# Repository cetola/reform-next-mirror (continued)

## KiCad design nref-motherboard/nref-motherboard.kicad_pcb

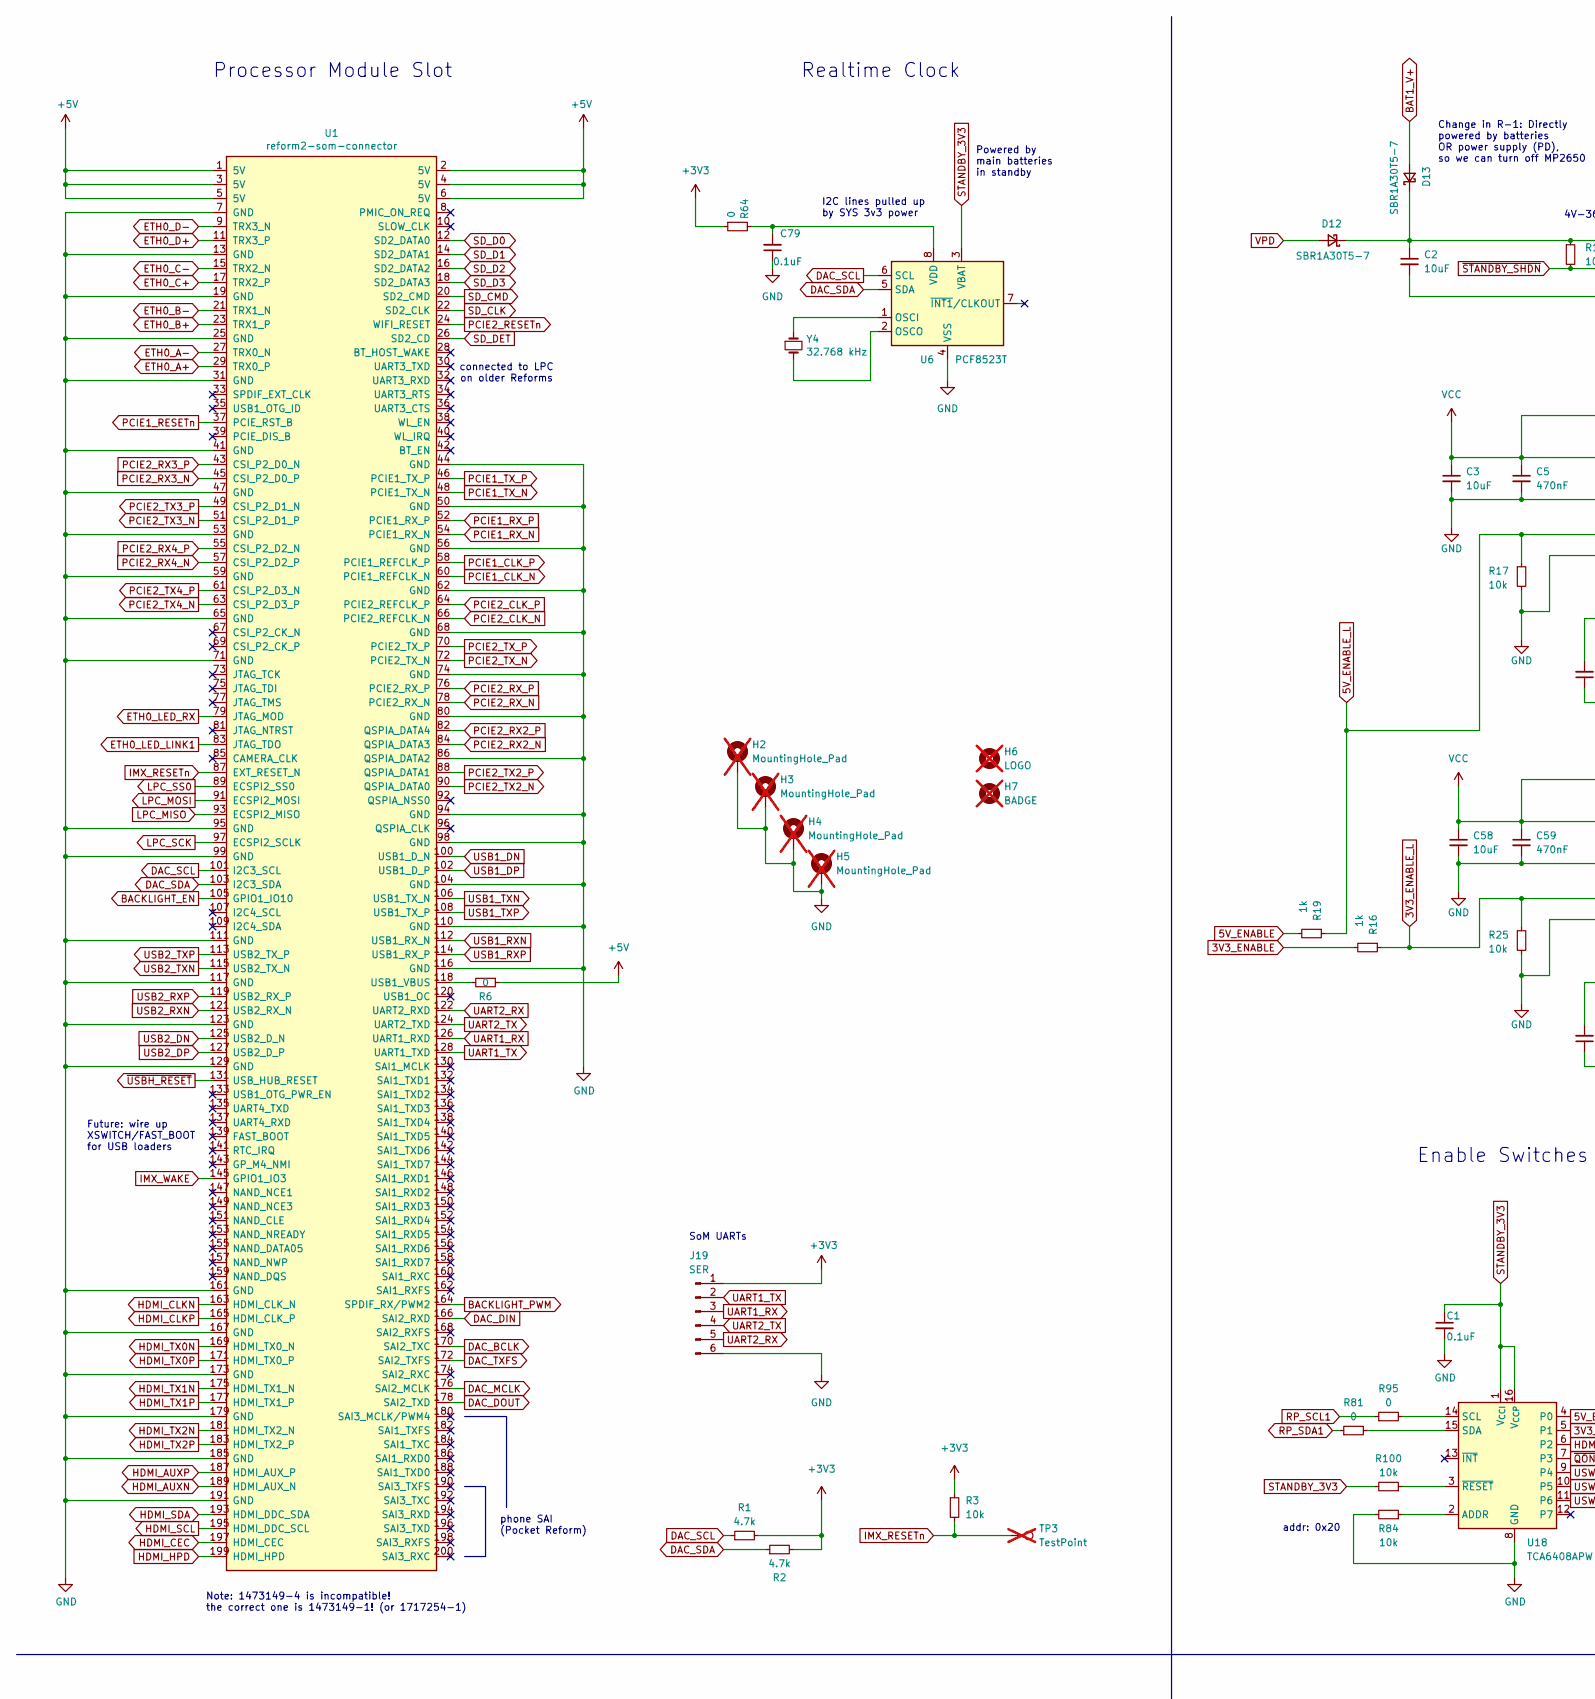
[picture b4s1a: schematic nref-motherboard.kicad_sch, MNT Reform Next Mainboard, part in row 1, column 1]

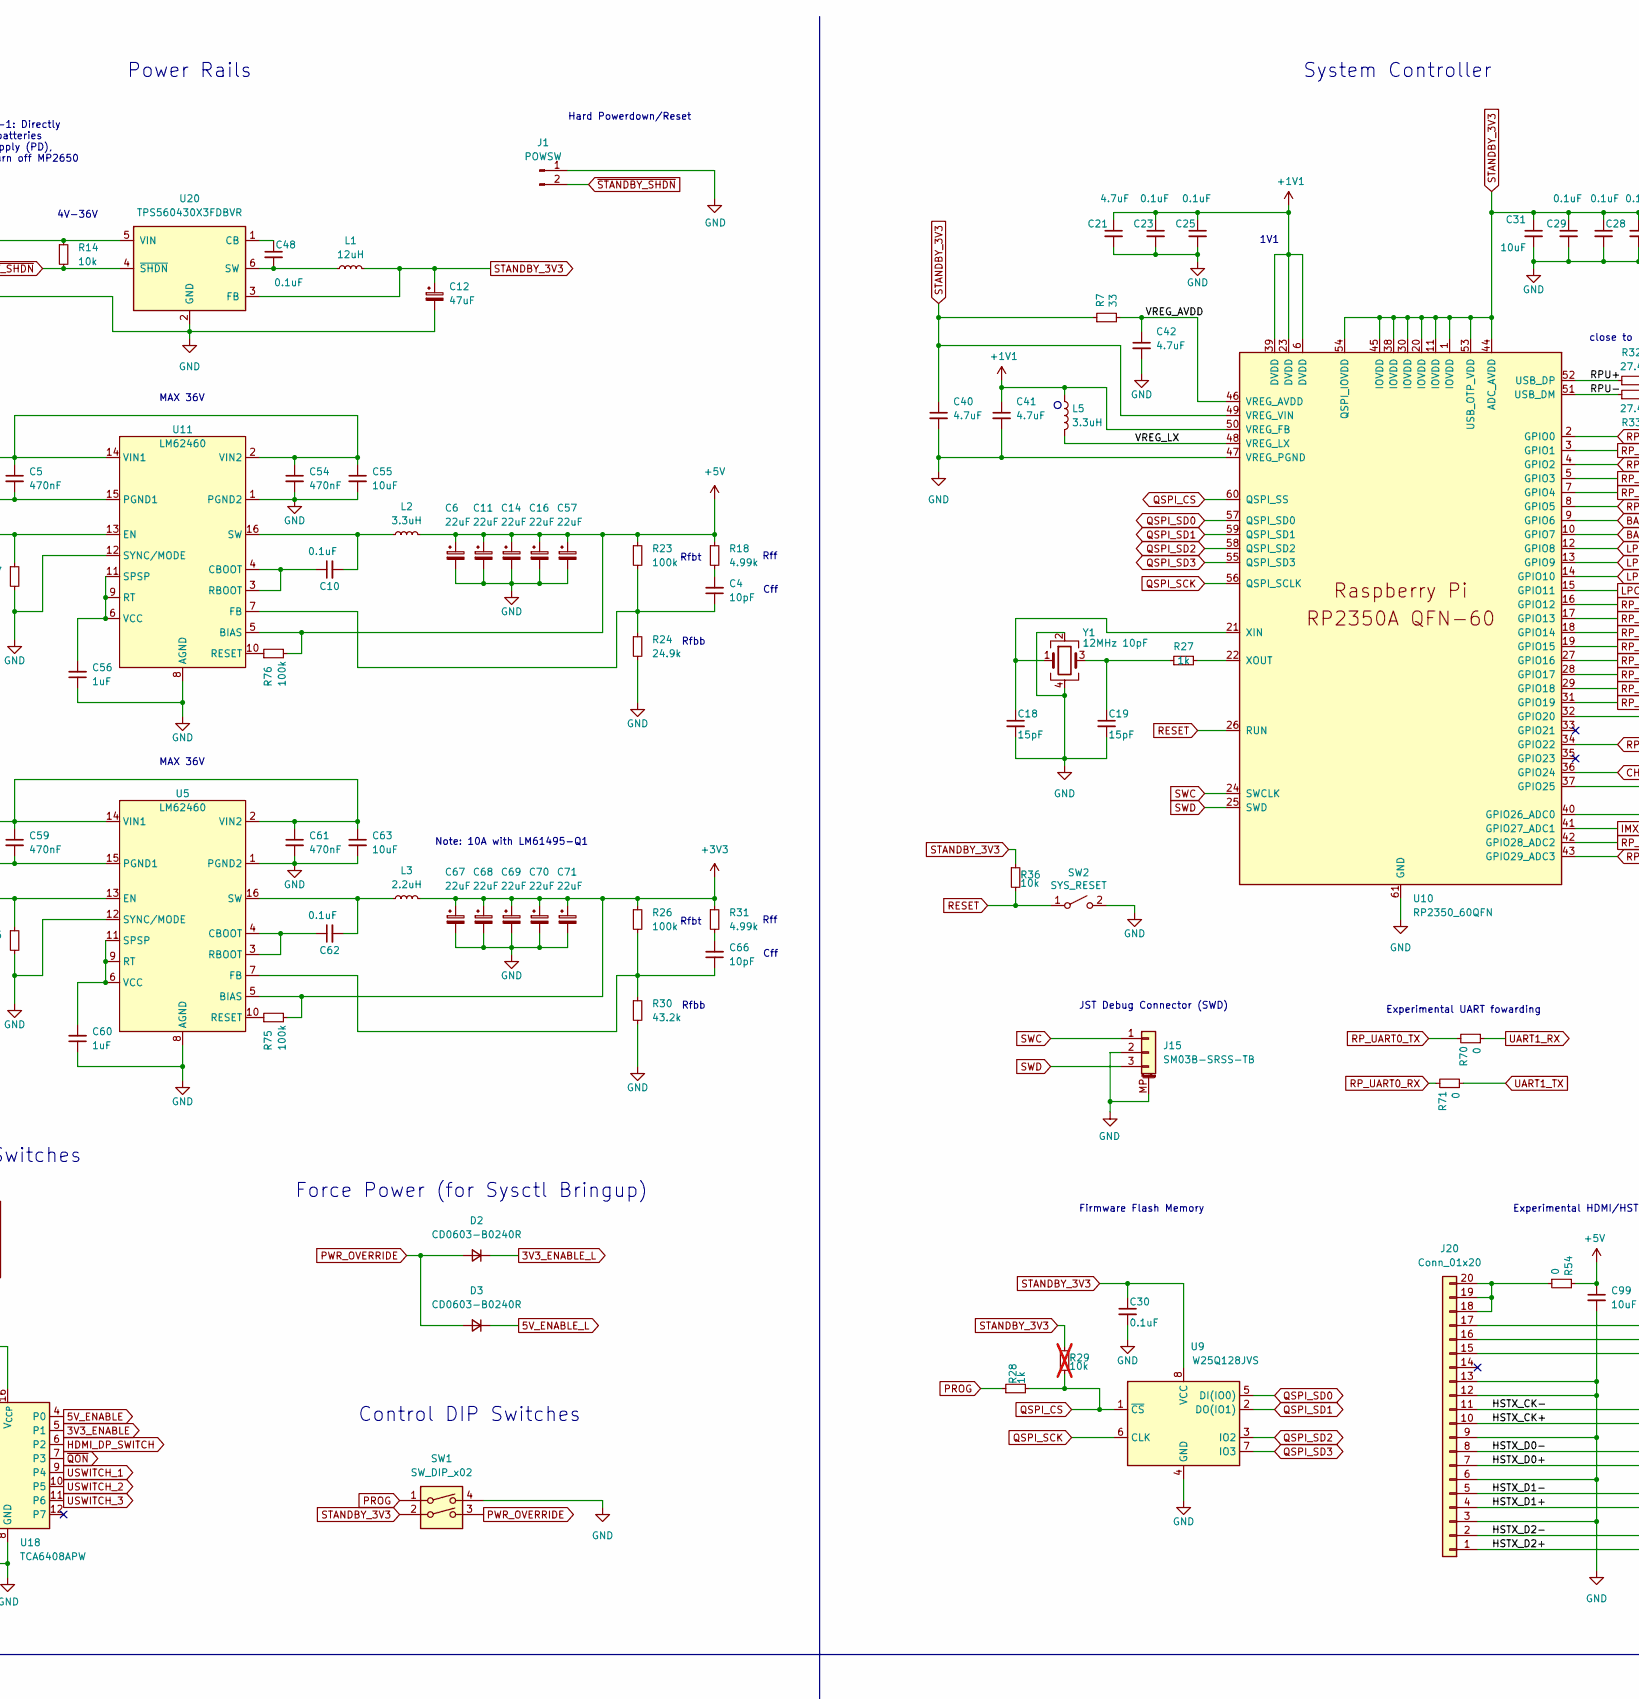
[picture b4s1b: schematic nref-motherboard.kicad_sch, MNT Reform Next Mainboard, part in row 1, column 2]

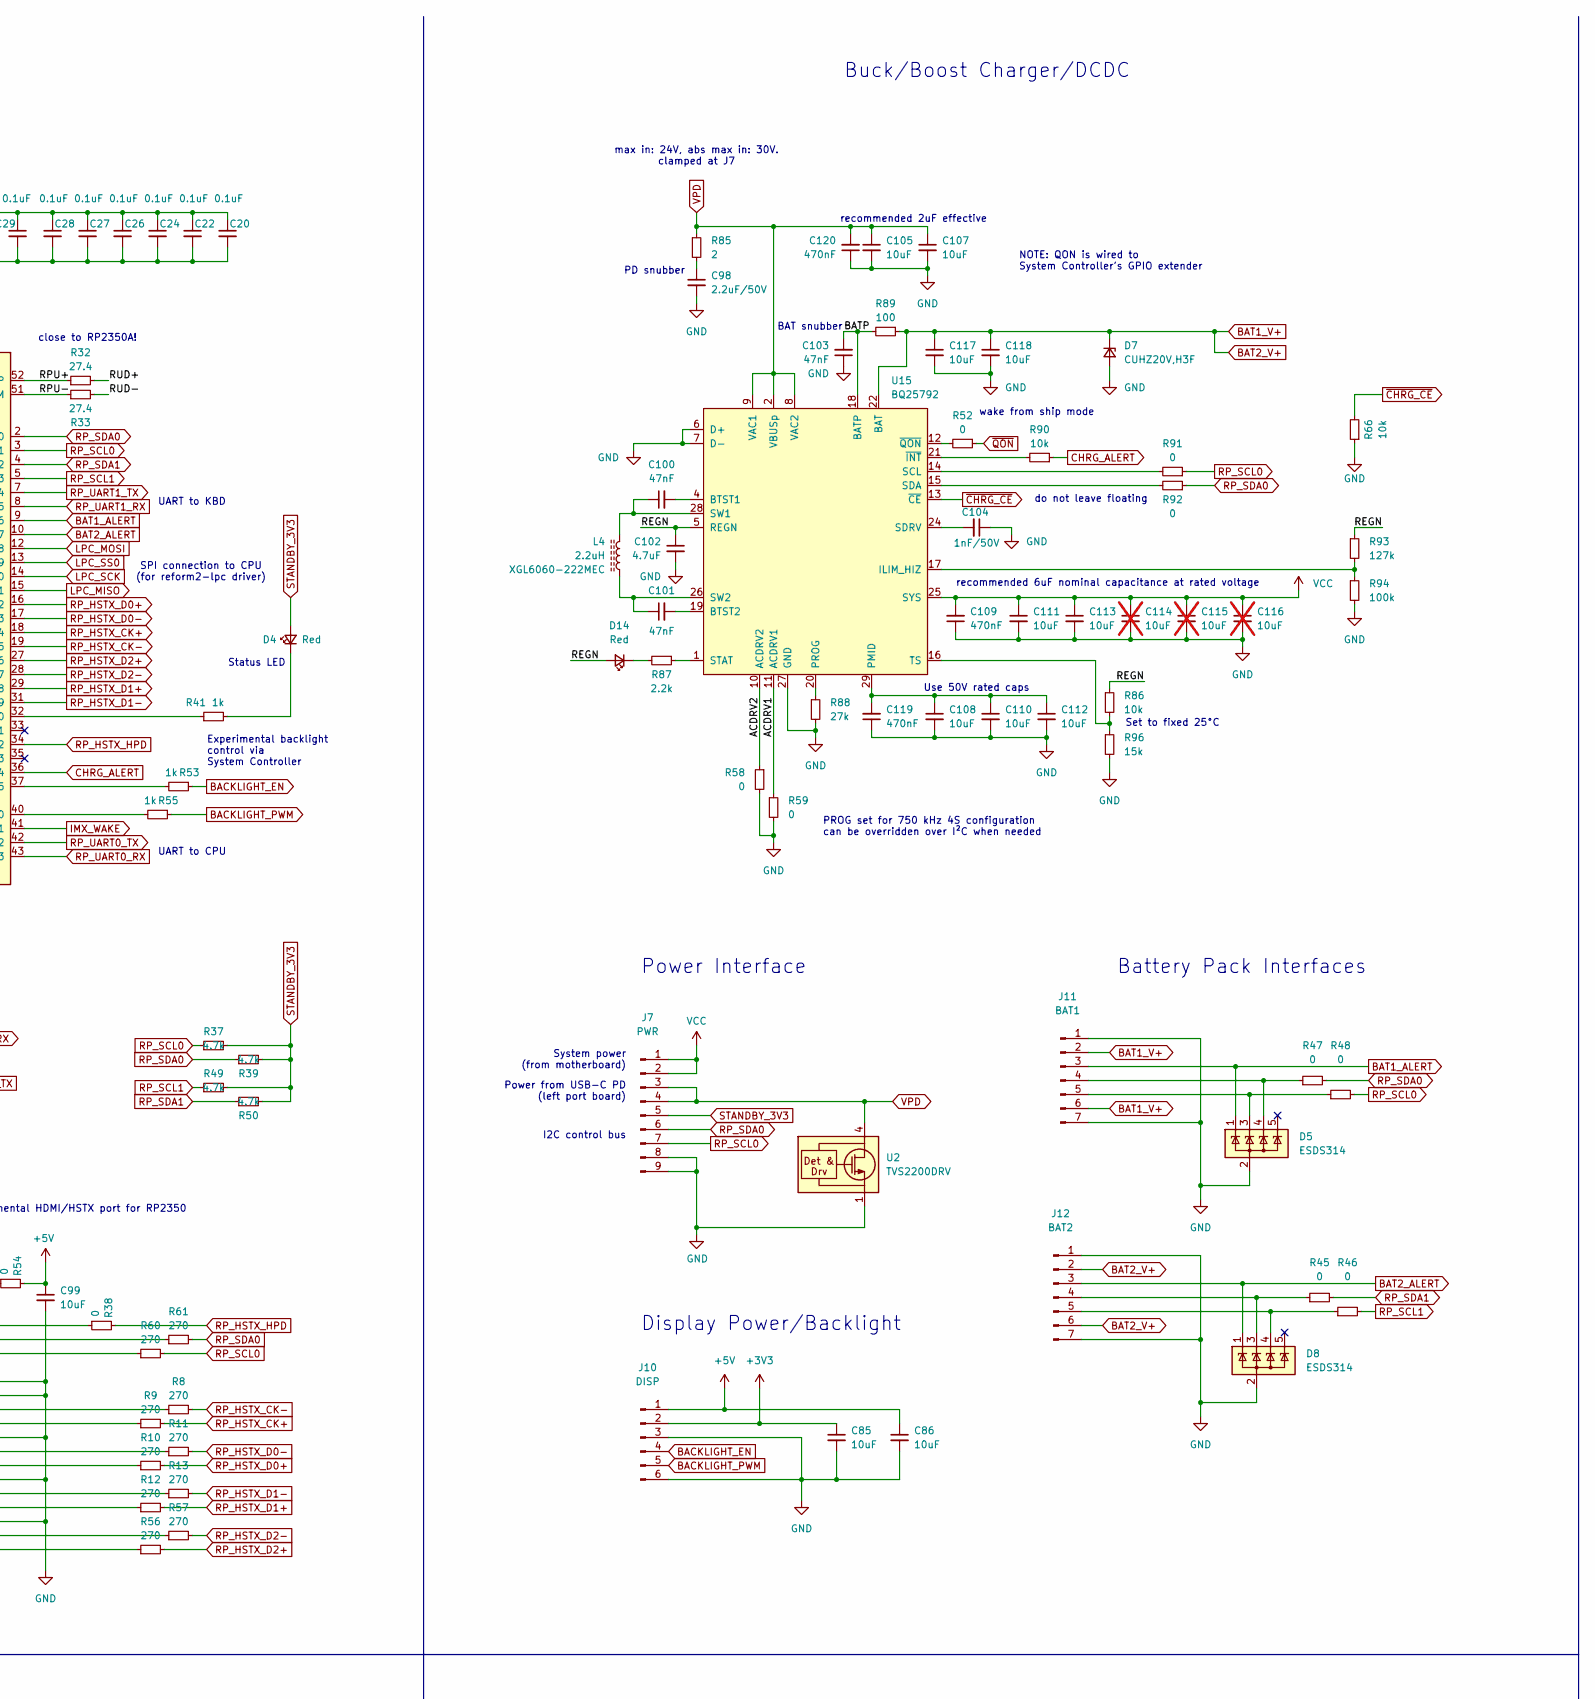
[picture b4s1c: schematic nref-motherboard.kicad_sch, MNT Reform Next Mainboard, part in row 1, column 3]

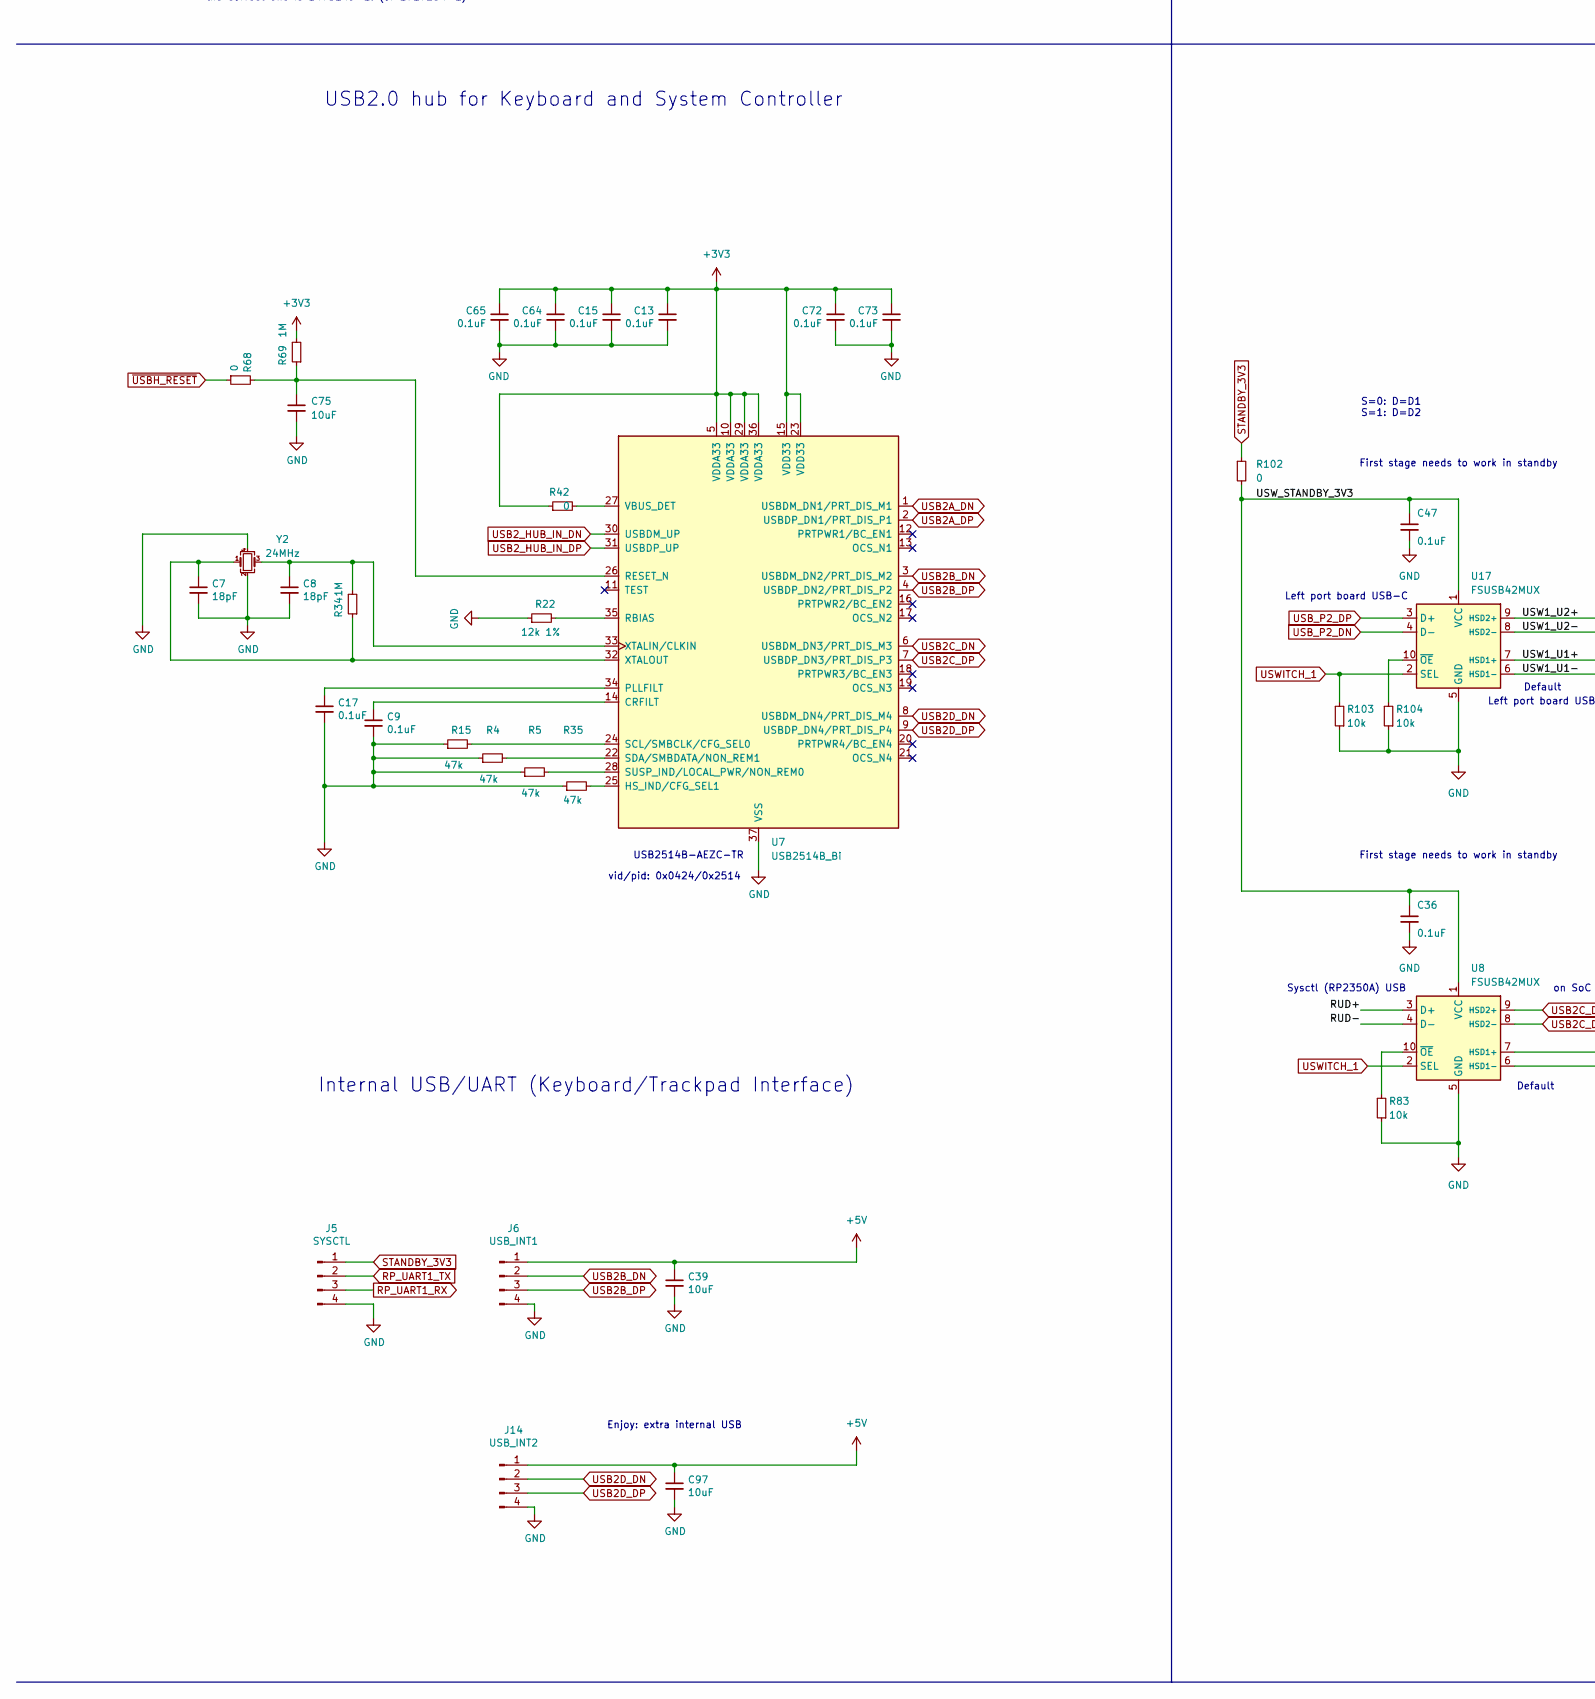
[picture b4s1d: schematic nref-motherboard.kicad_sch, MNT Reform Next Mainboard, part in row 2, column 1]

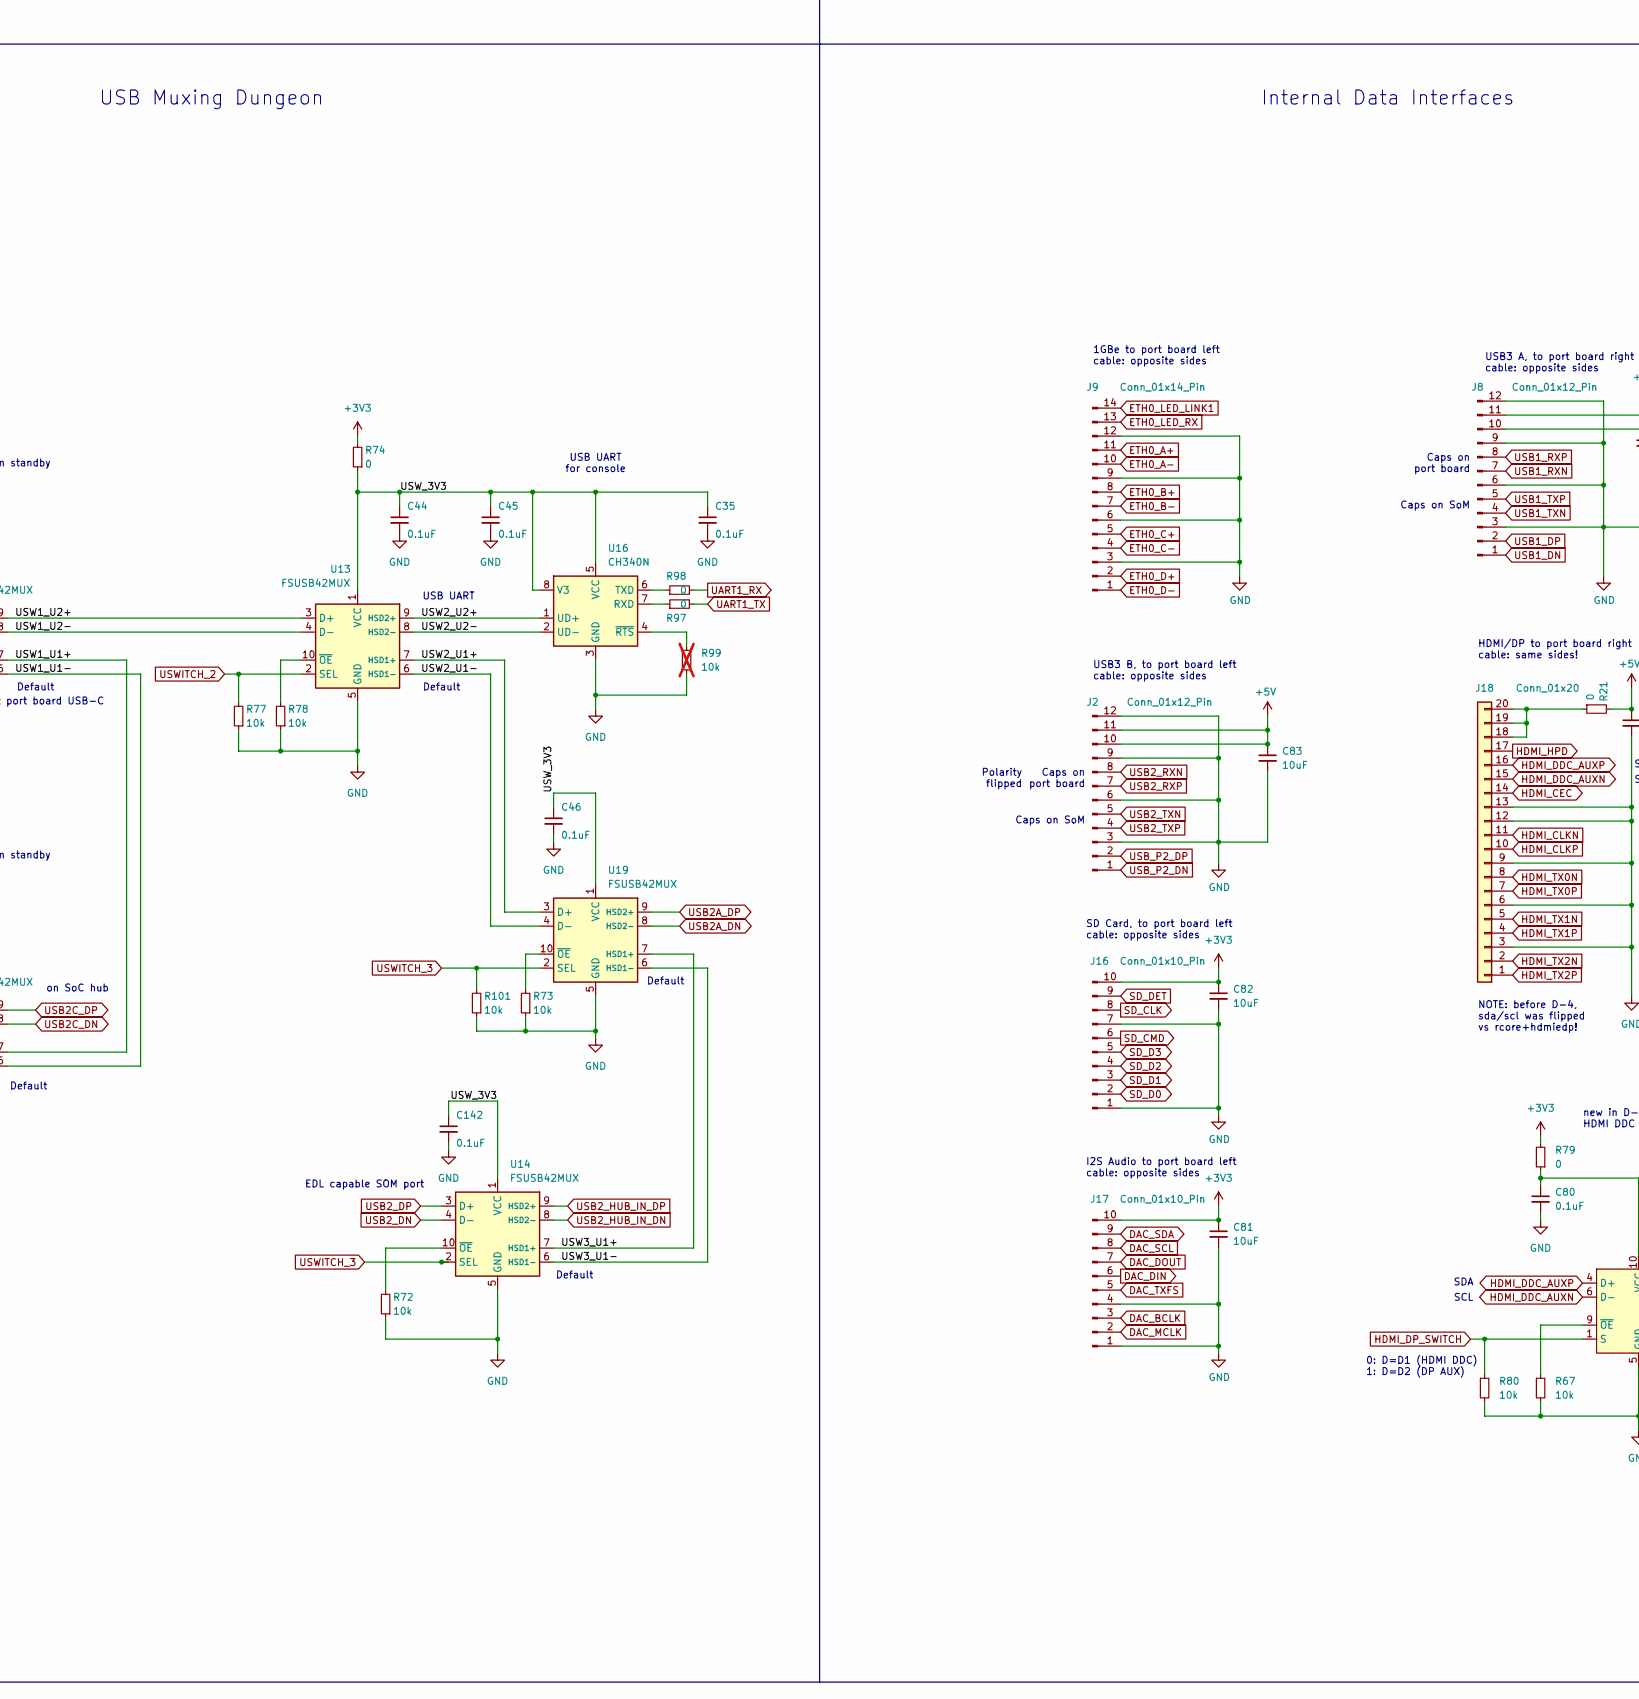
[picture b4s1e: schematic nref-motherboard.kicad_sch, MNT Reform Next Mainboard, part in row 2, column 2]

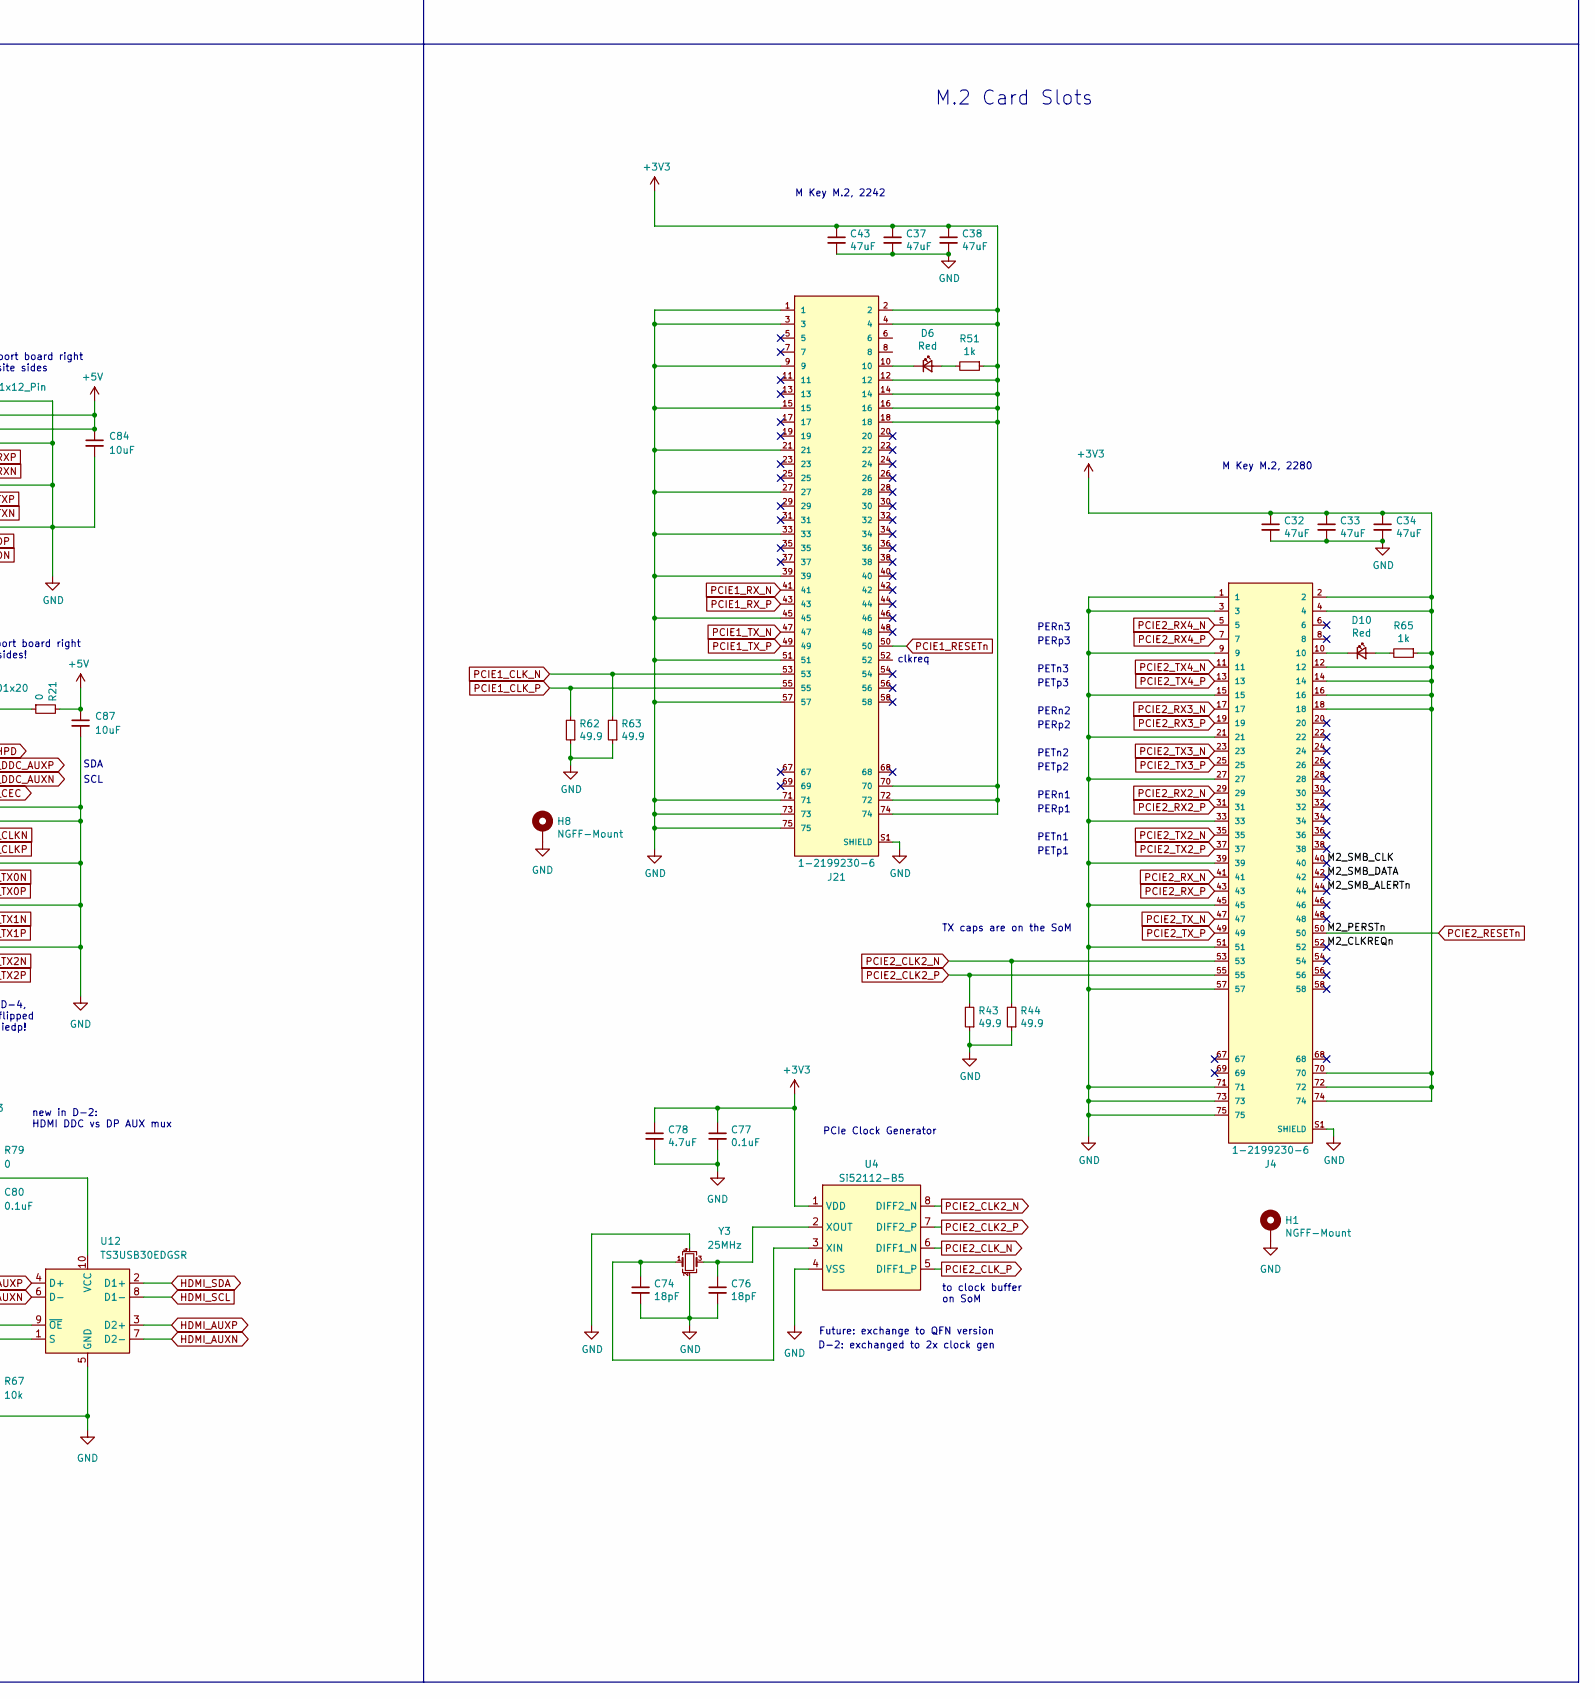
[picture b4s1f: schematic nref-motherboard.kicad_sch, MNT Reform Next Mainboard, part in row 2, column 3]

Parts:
C1, C9, C10, C13, C15, C17, C20, C22, C23, C24, C25, C26, C27, C28, C29, C30, C35, C36, C44, C45, C46, C47, C48, C62, C64, C65, C72, C73, C77, C79, C80, C142: 0.1uF; C_0402_1005Metric; LCSC C1525
C2, C3, C31, C39, C55, C58, C63, C75, C81, C82, C83, C84, C85, C86, C87, C97, C99: 10uF; C_0603_1608Metric; LCSC C92487
C4, C66: 10pF; C_0402_1005Metric; LCSC C32949
C5, C54, C59, C61: 470nF; C_0603_1608Metric; LCSC C170149
C6, C11, C14, C16, C57, C67, C68, C69, C70, C71: 22uF; C_0603_1608Metric; LCSC C361061
C7, C8, C74, C76: 18pF; C_0402_1005Metric; LCSC C1549
C12, C32, C33, C34, C37, C38, C43: 47uF; C_0603_1608Metric; LCSC C140782
C18, C19: 15pF; C_0603_1608Metric; LCSC C1644
C21, C41: 4.7uF; C_0603_1608Metric; LCSC C19666
C40, C42, C78, C102: 4.7uF; C_0402_1005Metric; LCSC C23733
C56, C60: 1uF; C_0402_1005Metric; LCSC C52923
C98: 2.2uF/50V; C_1206_3216Metric; LCSC C50254
C100, C101, C103: 47nF; C_0402_1005Metric; LCSC C272875
C104: 1nF/50V; C_0402_1005Metric; LCSC C1523
C105, C107, C108, C110, C112, C117, C118: 10uF; C_0805_2012Metric; LCSC C440198
C109, C119, C120: 470nF; C_0402_1005Metric; LCSC C437527
C111, C113: 10uF; C_1206_3216Metric; LCSC C13585
C114, C115, C116: 10uF; C_0603_1608Metric; not fitted
D2, D3: CD0603-B0240R; D_0603_1608Metric; LCSC C3312582
D4, D6, D10, D14: Red; LED_0603_1608Metric; LCSC C83242
D5, D8: ESDS314; SOT-23-5; LCSC C1847859
D7: CUHZ20V,H3F; D_SOD-323; LCSC C2857019
D12, D13: SBR1A30T5-7; D_SOD-323; LCSC C53100376
H1, H8: NGFF-Mount; WA-SMSI-M2; LCSC C22431324
H2, H3, H4, H5: MountingHole_Pad; MountingHole_2.5mm_Pad; not fitted
H6: LOGO; nref-logo; not fitted
H7: BADGE; nref-motherboard-badge; not fitted
J1: POWSW; JST_SH_SM02B-SRSS-TB_1x02-1MP_P1.00mm_Horizontal; LCSC C160402
J2, J8: Conn_01x12_Pin; Hirose_FH12-12S-0.5SH_1x12-1MP_P0.50mm_Horizontal; LCSC C2906115
J4, J21: 1-2199230-6; TE_1-2199230-6; LCSC C4710843
J5: SYSCTL; JST_SH_SM04B-SRSS-TB_1x04-1MP_P1.00mm_Horizontal; LCSC C160404
J6: USB_INT1; JST_SH_SM04B-SRSS-TB_1x04-1MP_P1.00mm_Horizontal; LCSC C160404
J7: PWR; JST_SH_SM09B-SRSS-TB_1x09-1MP_P1.00mm_Horizontal; LCSC C160408
J9: Conn_01x14_Pin; Hirose_FH12-14S-0.5SH_1x14-1MP_P0.50mm_Horizontal; LCSC C2906116
J10: DISP; JST_SH_SM06B-SRSS-TB_1x06-1MP_P1.00mm_Horizontal; LCSC C160405
J11: BAT1; JST_SH_SM07B-SRSS-TB_1x07-1MP_P1.00mm_Horizontal; LCSC C160406
J12: BAT2; JST_SH_SM07B-SRSS-TB_1x07-1MP_P1.00mm_Horizontal; LCSC C160406
J14: USB_INT2; JST_SH_SM04B-SRSS-TB_1x04-1MP_P1.00mm_Horizontal; LCSC C160404
J15: SM03B-SRSS-TB; JST_SH_SM03B-SRSS-TB_1x03-1MP_P1.00mm_Horizontal; LCSC C160403
J16, J17: Conn_01x10_Pin; Hirose_FH12-10S-0.5SH_1x10-1MP_P0.50mm_Horizontal; LCSC C2906114
J18, J20: Conn_01x20; Hirose_FH12-20S-0.5SH_1x20-1MP_P0.50mm_Horizontal; LCSC C2906119
J19: SER; JST_SH_SM06B-SRSS-TB_1x06-1MP_P1.00mm_Horizontal; LCSC C160405
L1: 12uH; L_Taiyo-Yuden_NR-30xx; LCSC C167758
L2: 3.3uH; L_Coilcraft_XAL6060-XXX; LCSC C3040366
L3: 2.2uH; L_Coilcraft_XAL6060-XXX; LCSC C167218
L4: 2.2uH; L_Coilcraft_XAL6060-XXX; MPN XGL6060-222MEC; LCSC C3911671
L5: 3.3uH; L_pol_2016; LCSC C42411119
R1, R2, R37, R39, R49, R50: 4.7k; R_0402_1005Metric; LCSC C25900
R3, R14, R17, R25, R36, R66, R67, R72, R73, R77, R78, R80, R83, R84, R86, R90, R100, R101, R103, R104: 10k; R_0402_1005Metric; LCSC C25744
R4, R5, R15, R35: 47k; R_0402_1005Metric; LCSC C25792
R6, R21, R38, R42, R45, R46, R47, R48, R52, R54, R58, R59, R64, R68, R70, R71, R74, R79, R81, R91, R92, R95, R97, R98, R102: 0; R_0402_1005Metric; LCSC C17168
R7: 33; R_0402_1005Metric; LCSC C25105
R8, R9, R10, R11, R12, R13, R56, R57, R60, R61: 270; R_0402_1005Metric; LCSC C25099
R16, R19, R27, R28, R41, R51, R53, R55, R65: 1k; R_0402_1005Metric; LCSC C11702
R18, R31: 4.99k; R_0402_1005Metric; LCSC C25903
R22: 12k 1%; R_0402_1005Metric; LCSC C25752
R23, R26, R75, R76: 100k; R_0402_1005Metric; LCSC C25741
R24: 24.9k; R_0402_1005Metric; LCSC C25874
R29: 10k; R_0402_1005Metric; LCSC C60490; not fitted
R30: 43.2k; R_0402_1005Metric; LCSC C25894
R32, R33: 27.4; R_0402_1005Metric; LCSC C31439
R34, R69: 1M; R_0402_1005Metric; LCSC C26083
R43, R44, R62, R63: 49.9; R_0402_1005Metric; LCSC C25120
R85: 2; R_0603_1608Metric; LCSC C22977
R87: 2.2k; R_0402_1005Metric; LCSC C25879
R88: 27k; R_0402_1005Metric; LCSC C25771
R89: 100; R_0402_1005Metric; LCSC C25076
R93: 127k; C_0603_1608Metric; LCSC C22869
R94: 100k; C_0603_1608Metric; LCSC C25803
R96: 15k; R_0402_1005Metric; LCSC C25756
R99: 10k; R_0402_1005Metric; LCSC C25744; not fitted
SW1: SW_DIP_x02; SW_DIP_SPSTx02_Slide_KingTek_DSHP02TJ_W5.25mm_P1.27mm_JPin; LCSC C3293149
SW2: SYS_RESET; SW_Push_1P1T_NO_CK_KMR2; LCSC C2689696
TP3: TestPoint; TestPoint_Pad_D1.0mm; not fitted
U1: reform2-som-connector; TE_1473149-4; LCSC C590722
U2: TVS2200DRV; WSON-6-1EP_2x2mm_P0.65mm_EP1x1.6mm; LCSC C523793
U4: Si52112-B5; TSSOP-8_4.4x3mm_P0.65mm; LCSC C1540577
U5, U11: LM62460; CONV_LM61495QRPHRQ1; LCSC C3198091
U6: PCF8523T; SOIC-8_3.9x4.9mm_P1.27mm; LCSC C2651516
U7: USB2514B_Bi; QFN-36-1EP_6x6mm_P0.5mm_EP3.7x3.7mm; LCSC C220807
U8, U13, U14, U17, U19: FSUSB42MUX; MSOP-10_3x3mm_P0.5mm; LCSC C11355
U9: W25Q128JVS; SOIC-8_5.23x5.23mm_P1.27mm; LCSC C179173
U10: RP2350_60QFN; RP2350-QFN-60-1EP_7x7_P0.4mm_EP3.4x3.4mm_ThermalVias; LCSC C42411118
U12: TS3USB30EDGSR; VSSOP-10_3x3mm_P0.5mm; LCSC C131998
U15: BQ25792; Texas_VQFN-HR_RQM_4x4mm_P0.40-0.45mm; LCSC C2862876
U16: CH340N; SOIC-8_3.9x4.9mm_P1.27mm; LCSC C2977777
U18: TCA6408APW; TSSOP-16_4.4x5mm_P0.65mm; LCSC C206177
U20: TPS560430X3FDBVR; SOT-23-6; LCSC C2071721
Y1: 12MHz 10pF; Crystal_SMD_3225-4Pin_3.2x2.5mm; LCSC C20625731
Y2: 24MHz; Crystal_SMD_3225-4Pin_3.2x2.5mm; LCSC C91744
Y3: 25MHz; Crystal_SMD_3225-4Pin_3.2x2.5mm; LCSC C2939753
Y4: 32.768 kHz; Crystal_SMD_3215-2Pin_3.2x1.5mm; LCSC C48615

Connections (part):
3V3_ENABLE: R16.2, U18.5 (P1)
3V3_ENABLE_L: D2.1 (K), R16.1, R25.1, U5.13 (EN)
5V_ENABLE: R19.2, U18.4 (P0)
5V_ENABLE_L: D3.1 (K), R17.1, R19.1, U11.13 (EN)
+1V1: C21.1, C23.1, C25.1, C41.1, L5.1, U10.6 (DVDD), U10.23 (DVDD), U10.39 (DVDD), U10.50 (VREG_FB)
+5V: C6.1, C11.1, C14.1, C16.1, C39.1, C57.1, C83.1, C84.1, C86.1, C87.1, C97.1, C99.1, J2.10, J2.11, J6.1, J8.10, J8.11, J10.1, J14.1, L2.2, R6.1, R18.1, R21.2, R23.1, R54.2, R76.2, U1.1 (5V), U1.2 (5V), U1.3 (5V), U1.4 (5V), U1.5 (5V), U1.6 (5V), U11.5 (BIAS)
/ACDRV1: R59.1, U15.11 (ACDRV1)
/ACDRV2: R58.1, U15.10 (ACDRV2)
/BATP: C103.2, R89.2, U15.18 (BATP)
/HSTX_CK+: J20.10, R9.1
/HSTX_CK-: J20.11, R8.1
/HSTX_D0+: J20.7, R10.1
/HSTX_D0-: J20.8, R11.1
/HSTX_D1+: J20.4, R12.1
/HSTX_D1-: J20.5, R13.1
/HSTX_D2+: J20.1, R56.1
/HSTX_D2-: J20.2, R57.1
/M2_CLKREQn: J4.52
/M2_SMB_ALERTn: J4.44
/M2_SMB_CLK: J4.40
/M2_SMB_DATA: J4.42
/REGN: C102.1, D14.2 (A), R86.1, R93.1, U15.5 (REGN)
/RPU+: R32.1, U10.52 (USB_DP)
/RPU-: R33.1, U10.51 (USB_DM)
/RUD+: R32.2, U8.3 (D+)
/RUD-: R33.2, U8.4 (D-)
/USW1_U1+: U8.7 (HSD1+), U17.7 (HSD1+)
/USW1_U1-: U8.6 (HSD1-), U17.6 (HSD1-)
/USW1_U2+: U13.3 (D+), U17.9 (HSD2+)
/USW1_U2-: U13.4 (D-), U17.8 (HSD2-)
/USW2_U1+: U13.7 (HSD1+), U19.3 (D+)
/USW2_U1-: U13.6 (HSD1-), U19.4 (D-)
/USW2_U2+: U13.9 (HSD2+), U16.1 (UD+)
/USW2_U2-: U13.8 (HSD2-), U16.2 (UD-)
/USW3_U1+: U14.7 (HSD1+), U19.7 (HSD1+)
/USW3_U1-: U14.6 (HSD1-), U19.6 (HSD1-)
/USW_STANDBY_3V3: C36.1, C47.1, R102.2, U8.1 (VCC), U17.1 (VCC)
/VREG_AVDD: C42.1, R7.2, U10.46 (VREG_AVDD)
/VREG_LX: L5.2, U10.48 (VREG_LX)
BACKLIGHT_EN: J10.4, R53.1, U1.105 (GPIO1_IO10)
BACKLIGHT_PWM: J10.5, R55.1, U1.164 (SPDIF_RX/PWM2)
BAT1_ALERT: D5.1 (K), J11.3, U10.9 (GPIO6)
BAT1_V+: C117.1, C118.1, D7.1 (K), D13.2 (A), J11.2, J11.6, J12.2, J12.6, R89.1, U15.22 (BAT), U15.23 (BAT)
BAT2_ALERT: D8.1 (K), J12.3, U10.10 (GPIO7)
CHRG_ALERT: R90.1, U10.36 (GPIO24)
DAC_BCLK: J17.3, U1.170 (SAI2_TXC)
DAC_DIN: J17.6, U1.166 (SAI2_RXD)
DAC_DOUT: J17.7, U1.178 (SAI2_TXD)
DAC_MCLK: J17.2, U1.176 (SAI2_MCLK)
DAC_SCL: J17.8, R1.1, U1.101 (I2C3_SCL), U6.6 (SCL)
DAC_SDA: J17.9, R2.1, U1.103 (I2C3_SDA), U6.5 (SDA)
DAC_TXFS: J17.5, U1.172 (SAI2_TXFS)
ETH0_A+: J9.11, U1.29 (TRX0_P)
ETH0_A-: J9.10, U1.27 (TRX0_N)
ETH0_B+: J9.8, U1.23 (TRX1_P)
ETH0_B-: J9.7, U1.21 (TRX1_N)
ETH0_C+: J9.5, U1.17 (TRX2_P)
ETH0_C-: J9.4, U1.15 (TRX2_N)
ETH0_D+: J9.2, U1.11 (TRX3_P)
ETH0_D-: J9.1, U1.9 (TRX3_N)
ETH0_LED_LINK1: J9.14, U1.83 (JTAG_TDO)
ETH0_LED_RX: J9.13, U1.79 (JTAG_MOD)
GND: C1.2, C2.2, C3.2, C5.2, C6.2, C7.2, C8.2, C9.2, C11.2, C12.2, C13.2, C14.2, C15.2, C16.2, C17.2, C18.2, C19.2, C20.2, C21.2, C22.2, C23.2, C24.2, C25.2, C26.2, C27.2, C28.2, C29.2, C30.2, C31.2, C32.2, C33.2, C34.2, C35.2, C36.2, C37.2, C38.2, C39.2, C40.2, C41.2, C42.2, C43.2, C44.2, C45.2, C46.2, C47.2, C54.2, C55.2, C56.1, C57.2, C58.2, C59.2, C60.1, C61.2, C63.2, C64.2, C65.2, C67.2, C68.2, C69.2, C70.2, C71.2, C72.2, C73.2, C74.2, C75.2, C76.2, C77.2, C78.2, C79.1, C80.2, C81.2, C82.2, C83.2, C84.2, C85.2, C86.2, C87.2, C97.2, C98.2, C99.2, C102.2, C103.1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
HDMI_AUXN: U1.189 (HDMI_AUX_N), U12.7 (D2-)
HDMI_AUXP: U1.187 (HDMI_AUX_P), U12.3 (D2+)
HDMI_CEC: J18.14, U1.197 (HDMI_CEC)
HDMI_CLKN: J18.11, U1.163 (HDMI_CLK_N)
HDMI_CLKP: J18.10, U1.165 (HDMI_CLK_P)
HDMI_DDC_AUXN: J18.15, U12.6 (D-)
HDMI_DDC_AUXP: J18.16, U12.4 (D+)
HDMI_DP_SWITCH: R80.1, U12.1 (S), U18.6 (P2)
HDMI_HPD: J18.17, U1.199 (HDMI_HPD)
HDMI_SCL: U1.195 (HDMI_DDC_SCL), U12.8 (D1-)
HDMI_SDA: U1.193 (HDMI_DDC_SDA), U12.2 (D1+)
HDMI_TX0N: J18.8, U1.169 (HDMI_TX0_N)
HDMI_TX0P: J18.7, U1.171 (HDMI_TX0_P)
HDMI_TX1N: J18.5, U1.175 (HDMI_TX1_N)
HDMI_TX1P: J18.4, U1.177 (HDMI_TX1_P)
HDMI_TX2N: J18.2, U1.181 (HDMI_TX2_N)
HDMI_TX2P: J18.1, U1.183 (HDMI_TX2_P)
IMX_RESETn: R3.2, TP3.1, U1.87 (EXT_RESET_N)
IMX_WAKE: U1.145 (GPIO1_IO3), U10.41 (GPIO27_ADC1)
LPC_MISO: U1.93 (ECSPI2_MISO), U10.15 (GPIO11)
LPC_MOSI: U1.91 (ECSPI2_MOSI), U10.12 (GPIO8)
LPC_SCK: U1.97 (ECSPI2_SCLK), U10.14 (GPIO10)
LPC_SS0: U1.89 (ECSPI2_SS0), U10.13 (GPIO9)
unnamed: C4.2, R18.2
unnamed: C19.1, R27.1, Y1.3
unnamed: C66.2, R31.2
unnamed: C98.1, R85.2
unnamed: D4.1 (K), R41.2
unnamed: D6.2 (A), R51.2
unnamed: D6.1 (K), J21.10
unnamed: D10.2 (A), R65.2
unnamed: D10.1 (K), J4.10
unnamed: C2.1, D12.1 (K), D13.1 (K), R14.1, U20.5 (VIN)
unnamed: D14.1 (K), R87.2
unnamed: D5.4 (K), J11.4, R47.1
unnamed: D5.3 (K), J11.5, R48.1
unnamed: D8.3 (K), J12.4, R45.1
unnamed: D8.4 (K), J12.5, R46.1
unnamed: J18.18, J18.19, J18.20, R21.1
unnamed: J20.15, R60.1
unnamed: J20.16, R61.1
unnamed: J20.17, R38.1
unnamed: J20.18, J20.19, J20.20, R54.1
unnamed: R6.2, U1.118 (USB1_VBUS)
unnamed: C74.1, U4.3 (XIN), Y3.1
unnamed: C76.1, U4.2 (XOUT), Y3.3
unnamed: C62.1, U5.3 (RBOOT), U5.4 (CBOOT)
unnamed: C66.1, R26.2, R30.1, U5.7 (FB)
unnamed: R75.1, U5.10 (RESET)
unnamed: C60.2, U5.6 (VCC), U5.9 (RT), U5.11 (SPSP)
unnamed: C62.2, L3.1, U5.16 (SW)
unnamed: U6.1 (OSCI), Y4.1
unnamed: U6.2 (OSCO), Y4.2
unnamed: C79.2, R64.2, U6.8 (VDD)
unnamed: C9.1, U7.14 (CRFILT)
unnamed: R35.2, U7.25 (HS_IND/CFG_SEL1)
unnamed: C17.1, U7.34 (PLLFILT)
unnamed: R22.2, U7.35 (RBIAS)
unnamed: C75.1, R68.2, R69.1, U7.26 (RESET_N)
unnamed: R15.2, U7.24 (SCL/SMBCLK/CFG_SEL0)
unnamed: R4.2, U7.22 (SDA/SMBDATA/NON_REM1)
unnamed: R5.2, U7.28 (SUSP_IND/LOCAL_PWR/NON_REM0)
unnamed: R42.2, U7.27 (VBUS_DET)
unnamed: C8.1, R34.2, U7.33 (XTALIN/CLKIN), Y2.3
unnamed: C7.1, R34.1, U7.32 (XTALOUT), Y2.1
unnamed: R83.2, U8.10 (~OE)
unnamed: R41.1, U10.32 (GPIO20)
unnamed: R53.2, U10.37 (GPIO25)
unnamed: R55.2, U10.40 (GPIO26_ADC0)
unnamed: C18.1, U10.21 (XIN), Y1.1
unnamed: R27.2, U10.22 (XOUT)
unnamed: C10.1, U11.3 (RBOOT), U11.4 (CBOOT)
unnamed: C4.1, R23.2, R24.1, U11.7 (FB)
unnamed: R76.1, U11.10 (RESET)
unnamed: C56.2, U11.6 (VCC), U11.9 (RT), U11.11 (SPSP)
unnamed: C10.2, L2.1, U11.16 (SW)
unnamed: R67.1, U12.9 (~OE)
unnamed: R78.2, U13.10 (~OE)
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
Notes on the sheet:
Power Rails
Sysctl (RP2350A) USB
PERn3
vid/pid: 0x0424/0x2514
PETn3
SoM UARTs
Rff
PETp3
clkreq
Enable Switches
USB Muxing Dungeon
USB UART
to clock buffer on SoM
close to RP2350A!
EDL capable SOM port
PERp2
recommended 6uF nominal capacitance at rated voltage
on SoC hub
0: D=D1 (HDMI DDC) 1: D=D2 (DP AUX)
Caps on SoM
Experimental backlight control via System Controller
phone SAI (Pocket Reform)
Display Power/Backlight
NOTE: QON is wired to System Controller's GPIO extender
Buck/Boost Charger/DCDC
Realtime Clock
I2C control bus
Rfbt
SCL
SD Card, to port board left cable: opposite sides
PROG set for 750 kHz 4S configuration can be overridden over I²C when needed
UART to KBD
SDA
Cff
S=0: D=D1 S=1: D=D2
new in D-2: HDMI DDC vs DP AUX mux
I2S Audio to port board left cable: opposite sides
addr: 0x20
PD snubber
Hard Powerdown/Reset

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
